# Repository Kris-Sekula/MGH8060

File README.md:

# MGH8060
SC/MP INS8060-based microcomputer running National Industrial Basic Language (NIBL)

Here is an overview of the device:

And here is my assembled unit - hardware v1.2

## Bill of Materials

| Component type     | Reference | Description                                   | Quantity |
| ------------------ | --------- | --------------------------------------------- | -------- |
| PCB                |           | [Order from PCBWay](https://www.pcbway.com/project/shareproject/MGH8060_SC_MP_Microcomputer_731c2144.html)| 1        |
| Integrated Circuit | U1        | MAX232(A) - RS232 Driver, 16 pin DIP          | 1        | 
| Integrated Circuit | U2        | INS8060 - SC/MP II Microcontroller, 40 pin DIP    | 1        |
| Integrated Circuit | U3        | HM62256B - 32kb SRAM, 28 pin DIP    | 1        |
| Integrated Circuit | U4        | 74LS573 - high-speed octal latch, 20 pin DIP    | 1        |
| Integrated Circuit | U5        | 8255A - Programmable Peripheral Interface, 40 pin DIP    | 1        |
| Integrated Circuit | U6        | 27C512 - 64kb EPROM, 28 pin DIP    | 1        |
| Integrated Circuit | U7        | 74LS138 - 3-to-8 line decoder, 16 pin DIP    | 1        |
| Integrated Circuit | U8        | 74LS21 - Dual 4 -Input AND Logic, 14 pin DIP   | 1        |
| Integrated Circuit | U8        | 74LS04 - HEX Inverter, 14 pin DIP   | 1        |
| LED                | D1        | LED indicator, 3 mm                           | 1        |
| LED                | D2        | LED indicator, 3 mm                           | 1        |
| Diode                | D3        | 1N4002,  general-purpose diode    | 1        |
| Pin Header         | J1        | 2x17 header female, 2.54 mm pitch        | 1        |
| Connector         | J2        | Screw terminal        | 1        |
| Connector         | J3        | DB9 male        | 1        |
| Pin Header         | J4        | 1x6 pin header, 2.54 mm pitch, angle | 1 |
| Pin Header         | J5        | 2x25 header female, 2.54 mm pitch        | 1        |
| Pin Header         | J6        | 1x6 pin header, 2.54 mm pitch | 1 |
| Pin Header         | JP1        | 1x2 pin header, 2.54 mm pitch | 1 |
| Pin Header         | JP2-JP4        | 1x3 pin header, 2.54 mm pitch | 3 |
| Capacitor          | C8-C15   | 1 uF, 16V, electrolytic, 2.54 mm pitch                  | 5       |
| Capacitor          | C6       | 27pF, ceramic, 2.54 mm pitch                | 1        |
| Capacitor          | C8-C15   | 0.1 uF, 50V, MLCC, 5 mm pitch                 | 8        |
| Capacitor          | C7,C20   | 22uF, 6.8V, electrolytic, 2.54 mm pitch                | 2        |
| Resistor           | R1   | 160 kohm, 0.125 W, axial                       | 1        |
| Resistor           | R2-R4,R8   | 1 kohm, 0.125 W, axial                       | 4        |
| Resistor           | R5   | 10k kohm, 0.125 W, axial                       | 1        |
| Resistor           | R9   | 4.7k kohm, 0.125 W, axial                       | 1        |
| Crystal           | X1   | 4MHz, short 3.5mm heigh max                       | 1        |
| IC Socket          | U8,U9     | 14 pin DIP                                    | 2       |
| IC Socket          | U1,U7    | 16 pin DIP                                    | 2        |
| IC Socket          | U4     | 20 pin DIP                                    | 1        |
| IC Socket          | U3,U6     | 28 pin DIP                                    | 2        |
| IC Socket          | U2,U5     | 40 pin DIP                                    | 2        |

## Memory Map

| Start | End | RAM | ROM | I/O |
| :------: | :------: | :----: | :----: | :----: |
| 0x0000 | 0x1FFF |  | X |  |			
| 0x2000 | 0x3FFF | X |  |  |			
| 0x4000 | 0x5FFF | X |  |  |			
| 0x6000 | 0x7FFF | X |  |  |			
| 0x8000 | 0x9FFF |  | X |  |			
| 0xA000 | 0xBFFF |  |  | X |			
| 0xC000 | 0xDFFF |  | X |  |			
| 0xE000 | 0xFFFF |  | X |  |

| Address | 8255 Function |
| :---: | :---: |
| 0xA000 | Port A |
| 0xA001 | Port B |
| 0xA002 | Port C |
| 0xA003 | Ctrl Register |

### Schematic
[Schematic - Version 1.2](Hardware/mgh8060_v1.2.pdf)

### Credits
* The device is based on the work of [Ronald Dekker](https://www.dos4ever.com/SCMP/SCMP.html#circuit)

* Early versions of my design were reviewed by Phil(aka [Retro Phil](https://www.mccrash-racing.co.uk/philg/picl/picl.htm)) who offered a lot of helpful suggestions, he also contributed all the firmware for MGH8060

## Release Notes

I used HCT parts for most of the ICs. Power usage was about 60mA

I used Winbond W27C512 (EEPROM pin compatible with EPROMs)

Please consider getting the PCB from my sponsor PCBWay

If you found this helpful and you like the work I do, why not buy me a coffee, thanks! :)

### Changes
* Version 1.2:
  
  * Fixed missing connections. 

* Version 1.1:
  
  * Corrected CE signals (thanks Phil)

* Version 1.0
  
  * Initial version

## License

Copyright 2024 Kris Sekula

This work is licensed under a [Creative Commons Attribution-NonCommercial 4.0 International (CC BY-NC 4.0) ](https://creativecommons.org/licenses/by-nc/4.0/).

### Trademarks

* Other names and brands may be claimed as the property of others.

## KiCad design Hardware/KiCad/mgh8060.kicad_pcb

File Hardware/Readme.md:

In the KiCad folder, you can find the KiCad sources for the PCB v1.2. 

## __Before you download the files, please consider ordering the PCBs from *PCBWay* by following this [-> link <-](https://www.pcbway.com/project/shareproject/MGH8060_SC_MP_Microcomputer_731c2144.html).__

I get a small portion of your order that I can use towards my future open-source projects, and more importantly, PCBWay will be more likely to sponsor me again.

Thanks again to PCBWay for sponsoring the PCBs used in this project.

If you found this helpful and you like the work I do, why not buy me a coffee, thanks! :)

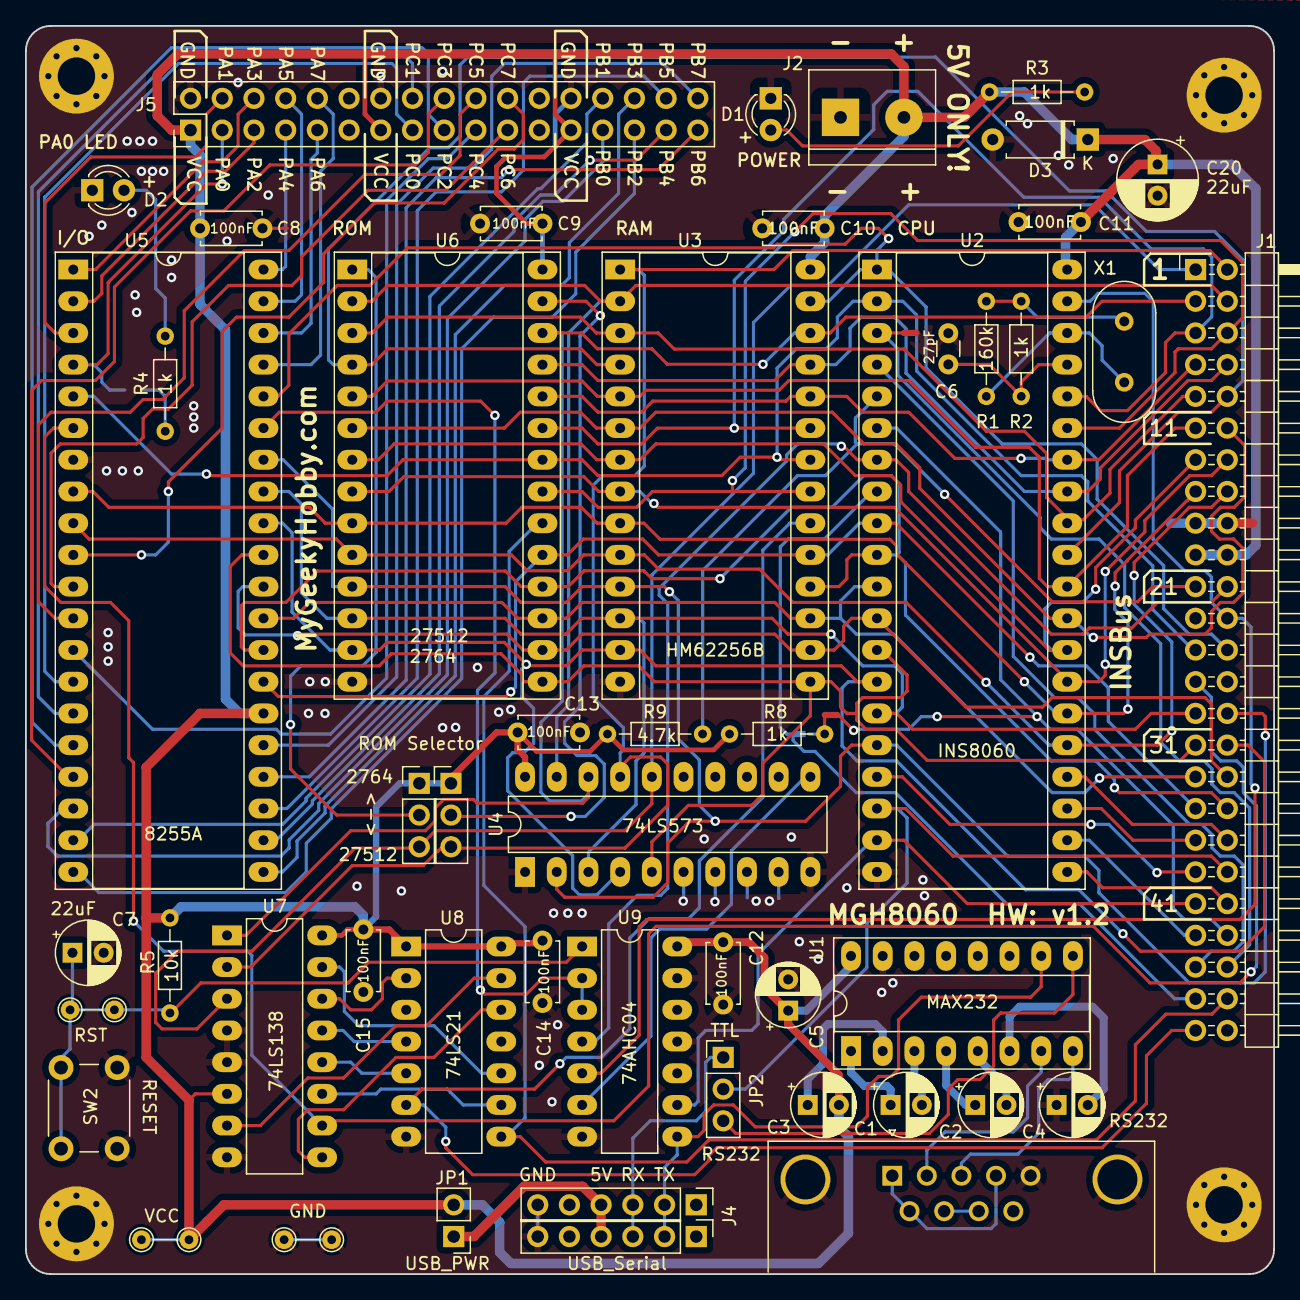
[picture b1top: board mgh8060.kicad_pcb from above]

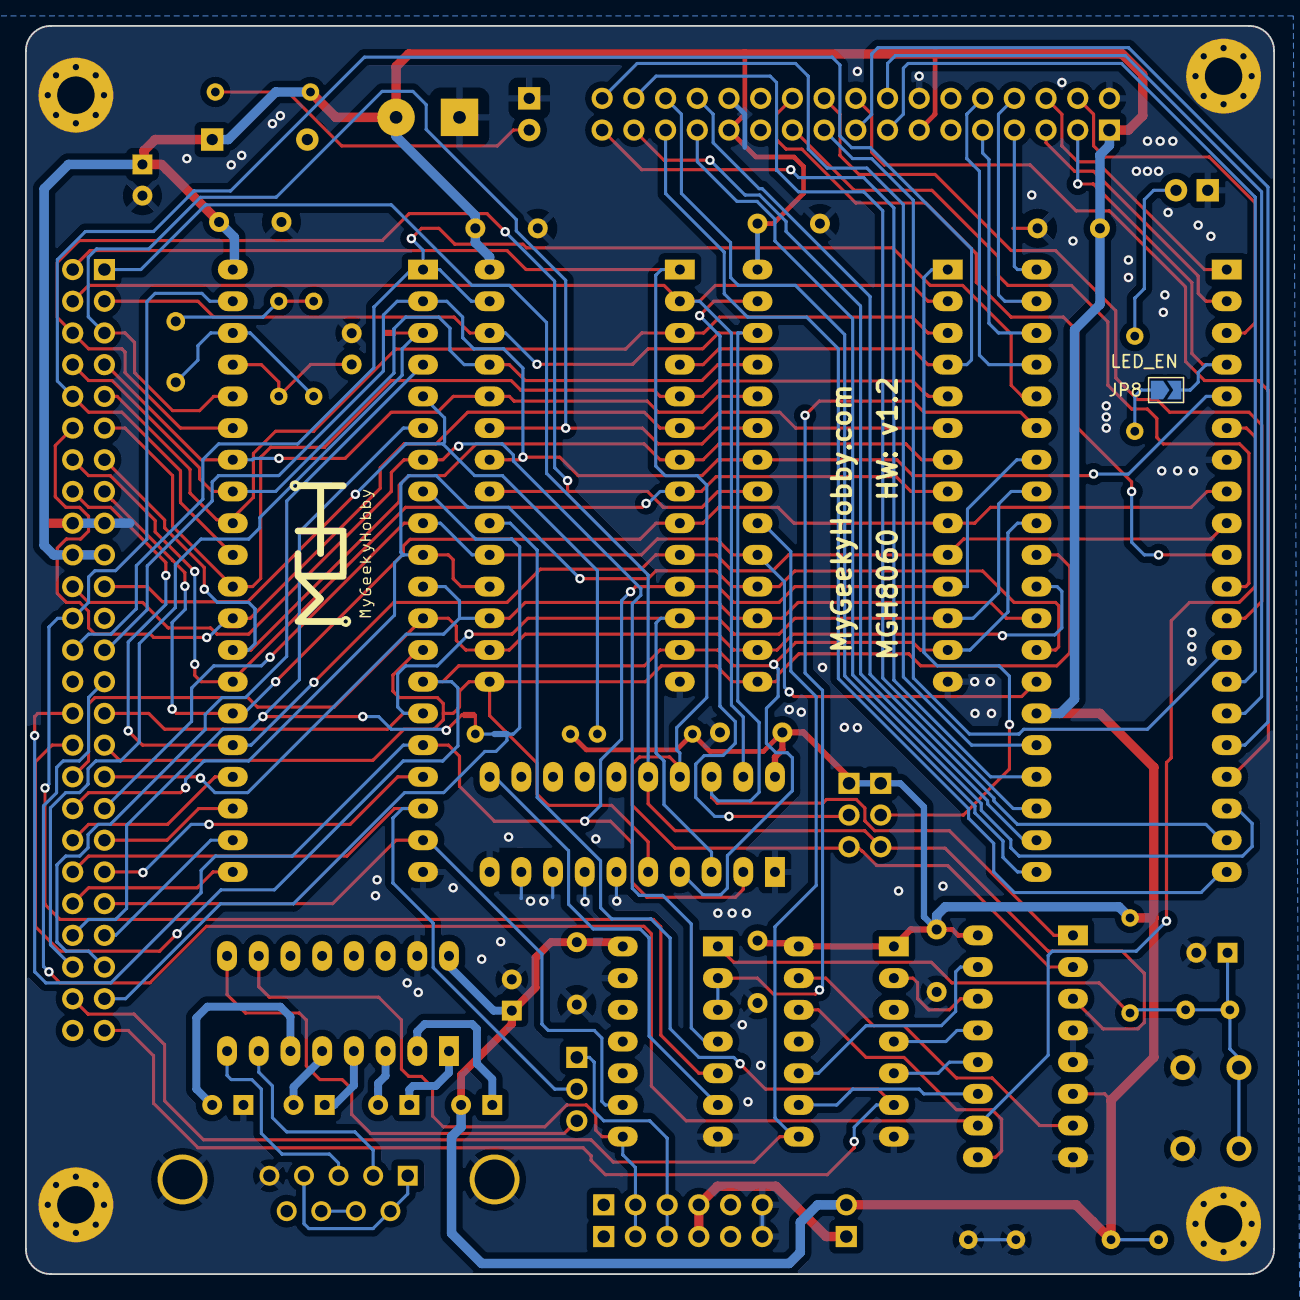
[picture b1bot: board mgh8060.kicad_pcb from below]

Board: 2 copper layers, 100.0 x 100.0 mm, 61 parts (2 on the bottom side), 102 nets.

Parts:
C1, C2, C3, C4, C5: 1uF; CP_Radial_D5.0mm_P2.50mm
C6: 27pF; C_Disc_D3.0mm_W1.6mm_P2.50mm
C7: 22uF; CP_Radial_D5.0mm_P2.50mm
C8, C9, C10, C11, C12, C13, C14, C15: 100nF; C_Disc_D4.7mm_W2.5mm_P5.00mm
C20: 22uF; CP_Radial_D6.3mm_P2.50mm
D1, D2: LED; LED_D3.0mm
D3: 1N4002; D_A-405_P7.62mm_Horizontal
H1, H2, H3, H4: MountingHole_Pad; MountingHole_3mm_Pad_Via
J1: Z80Bus; PinHeader_2x25_P2.54mm_Horizontal
J2: Screw_Terminal_01x02; TerminalBlock_bornier-2_P5.08mm
J3: DB9_Male; DSUB-9_Male_Horizontal_P2.77x2.84mm_EdgePinOffset4.94mm_Hou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
J4, J6: FTDI; PinHeader_1x06_P2.54mm_Vertical
J5: Conn_02x15_Odd_Even; PinHeader_2x17_P2.54mm_Vertical
JP1: VCC_EN; PinHeader_1x02_P2.54mm_Vertical
JP2: RX_Select; PinHeader_1x03_P2.54mm_Vertical
JP3: Pin27_Select; PinHeader_1x03_P2.54mm_Vertical
JP4: Pin1_Select; PinHeader_1x03_P2.54mm_Vertical
JP8: LED_EN; SolderJumper-2_P1.3mm_Open_TrianglePad1.0x1.5mm
NT1, NT2, NT3: NetTie_2; NetTie-2_SMD_Pad0.5mm
R1: 160k; R_Axial_DIN0204_L3.6mm_D1.6mm_P7.62mm_Horizontal
R2, R3, R4, R8: 1k; R_Axial_DIN0204_L3.6mm_D1.6mm_P7.62mm_Horizontal
R5: 10k; R_Axial_DIN0204_L3.6mm_D1.6mm_P7.62mm_Horizontal
R9: 4.7k; R_Axial_DIN0204_L3.6mm_D1.6mm_P7.62mm_Horizontal
SW2: SW_Push; SW_PUSH_6mm
TP1, TP3, TP7, TP8: 5V VCC; TestPoint_THTPad_D1.5mm_Drill0.7mm
TP2, TP4: GND; TestPoint_THTPad_D1.5mm_Drill0.7mm
U1: MAX232; DIP-16_W7.62mm_Socket_LongPads
U2: INS8060; DIP-40_W15.24mm_Socket_LongPads
U3: HM62256B; DIP-28_W15.24mm_Socket_LongPads
U4: 74LS573; DIP-20_W7.62mm_LongPads
U5: 8255A; DIP-40_W15.24mm_Socket_LongPads
U6: 27C512; DIP-28_W15.24mm_Socket_LongPads
U7: 74LS138; DIP-16_W7.62mm_LongPads
U8: 74LS21; DIP-14_W7.62mm_LongPads
U9: 74AHC04; DIP-14_W7.62mm_LongPads
X1: 4MHz; Crystal_HC49-U_Vertical

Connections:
/A0: J1.16 (A0), U2.25 (A0), U3.10 (A0), U5.9 (A0), U6.10 (A0)
/A1: J1.15 (A1), U2.26 (A1), U3.9 (A1), U5.8 (A1), U6.9 (A1)
/A2: J1.14 (A2), U2.27 (A2), U3.8 (A2), U6.8 (A2)
/A3: J1.13 (A3), U2.28 (A3), U3.7 (A3), U6.7 (A3)
/A4: J1.12 (A4), U2.29 (A4), U3.6 (A4), U6.6 (A4)
/A5: J1.11 (A5), U2.30 (A5), U3.5 (A5), U6.5 (A5)
/A6: J1.10 (A6), U2.31 (A6), U3.4 (A6), U6.4 (A6)
/A7: J1.9 (A7), U2.32 (A7), U3.3 (A7), U6.3 (A7)
/A8: J1.8 (A8), U2.33 (A8), U3.25 (A8), U6.25 (A8)
/A9: J1.7 (A9), U2.34 (A9), U3.24 (A9), U6.24 (A9)
/A10: J1.6 (A10), U2.35 (A10), U3.21 (A10), U6.21 (A10)
/A11: J1.5 (A11), U2.36 (A11), U3.23 (A11), U6.23 (A11)
/A12: J1.4 (A12), U3.2 (A12), U4.19 (Q0), U6.2 (A12)
/A13: J1.3 (A13), U3.26 (A13), U4.18 (Q1), U6.26 (A13), U7.1 (A0)
/A14: J1.2 (A14), JP3.3 (B), U3.1 (A14), U4.17 (Q2), U7.2 (A1)
/A15: J1.1 (A15), JP4.3 (B), U4.16 (Q3), U7.3 (A2)
/CONT: J1.47 (CONT), NT1.2, U2.8 (CONT)
/D0: J1.30 (D0), U2.16 (D0), U3.11 (D0), U4.2 (D0), U5.34 (D0), U6.11 (D0)
/D1: J1.29 (D1), U2.15 (D1), U3.12 (D1), U4.3 (D1), U5.33 (D1), U6.12 (D1)
/D2: J1.32 (D2), U2.14 (D2), U3.13 (D2), U4.4 (D2), U5.32 (D2), U6.13 (D2)
/D3: J1.31 (D3), U2.13 (D3), U3.15 (D3), U4.5 (D3), U5.31 (D3), U6.15 (D3)
/D4: J1.34 (D4), U2.12 (D4), U3.16 (D4), U5.30 (D4), U6.16 (D4)
/D5: J1.33 (D5), U2.11 (D5), U3.17 (D5), U5.29 (D5), U6.17 (D5)
/D6: J1.36 (D6), U2.10 (D6), U3.18 (D6), U5.28 (D6), U6.18 (D6)
/D7: J1.35 (D7), U2.9 (D7), U3.19 (D7), U5.27 (D7), U6.19 (D7)
/F0: J1.41 (F0), U2.19 (F0), U9.9
/F1: J1.42 (F1), U2.21 (F1)
/F2: J1.43 (F2), U2.22 (F2)
/PA0: J5.3, JP8.2 (B), U5.4 (PA0)
/PA1: J5.4, U5.3 (PA1)
/PA2: J5.5, U5.2 (PA2)
/PA3: J5.6, U5.1 (PA3)
/PA4: J5.7, U5.40 (PA4)
/PA5: J5.8, U5.39 (PA5)
/PA6: J5.9, U5.38 (PA6)
/PA7: J5.10, U5.37 (PA7)
/PB0: J5.27, U5.18 (PB0)
/PB1: J5.28, U5.19 (PB1)
/PB2: J5.29, U5.20 (PB2)
/PB3: J5.30, U5.21 (PB3)
/PB4: J5.31, U5.22 (PB4)
/PB5: J5.32, U5.23 (PB5)
/PB6: J5.33, U5.24 (PB6)
/PB7: J5.34, U5.25 (PB7)
/PC0: J5.15, U5.14 (PC0)
/PC1: J5.16, U5.15 (PC1)
/PC2: J5.17, U5.16 (PC2)
/PC3: J5.18, U5.17 (PC3)
/PC4: J5.19, U5.13 (PC4)
/PC5: J5.20, U5.12 (PC5)
/PC6: J5.21, U5.11 (PC6)
/PC7: J5.22, U5.10 (PC7)
/RESET: U5.35 (RESET), U9.2, U9.3
/ROM_1: JP4.2 (C), U6.1 (A15)
/ROM_27: JP3.2 (C), U6.27 (A14)
/RX_232: JP2.3 (B), U1.9 (R2OUT)
/RX_USB: J4.3, J6.3, JP2.1 (A)
/SA: J1.39 (SA), U2.17 (SA)
/SB: J1.40 (SB), JP2.2 (C), U2.18 (SB)
/SIN: J1.38 (SIN), U2.24 (SIN)
/SOUT: J1.37 (SOUT), U2.23 (SOUT)
/TX: J4.2, J6.2, U1.10 (T2IN), U9.8
/~ADS: J1.24 (~ADS), U2.39 (~ADS), U9.5
/~BREQ: J1.21 (~BREQ), R9.2, U2.5 (~BREQ)
/~ENIN: J1.46 (~ENIN), NT3.2, U2.3 (~ENIN)
/~ENOUT: J1.45 (~ENOUT), U2.4 (~ENOUT)
/~Ext_RESET: C7.1, R5.2, SW2.2, TP7.1, TP8.1, U9.1
/~HOLD: J1.44 (~HOLD), NT2.2, U2.6 (~HOLD)
/~IO_CS: J1.27 (~IO_CS), U5.6 (~CS), U7.10 (O5)
/~RAM_CS: J1.49 (USER2), U3.20 (~CS), U8.6
/~RDS: J1.25 (~MREQ), U2.2 (~RDS), U3.22 (~OE), U5.5 (~RD), U6.22 (~OE)
/~RESET: J1.22 (~Rst), U2.7 (~RST), U9.4
/~ROM_CS: J1.48 (USER1), U6.20 (~CE), U8.8
/~WDS: J1.26 (~WDS), U2.1 (~WDS), U3.27 (~WE), U5.36 (~WR)
GND: C4.1, C5.2, C6.2, C7.2, C8.2, C9.2, C10.2, C11.2, C12.2, C13.2, C14.2, C15.2, C20.2, D1.1 (K), D2.1 (K), D3.2 (A), H1.1, H2.1, H3.1, H4.1, J1.17 (GND), J1.18 (GND), J2.1, J3.0 (PAD), J3.5, J4.6, J5.2, J5.14, J5.26, J6.6, NT3.1, SW2.1, TP2.1, TP4.1, U1.15 (GND), U2.20 (GND), U3.14 (VSS), U4.1 (OE), U4.6 (D4), U4.7 (D5), U4.8 (D6), U4.9 (D7), U4.10 (GND), U5.7 (GND), U6.14 (GND), U7.4 (E1), U7.5 (E2), U7.8 (GND), U8.7 (GND), U9.7 (GND), U9.11, U9.13
unnamed: D1.2 (A), R3.2
unnamed: D2.2 (A), R4.2
unnamed: J3.1, J3.4, J3.6
unnamed: J3.7, J3.8
unnamed: J4.4, J6.4, JP1.1 (A)
unnamed: JP8.1 (A), R4.1
unnamed: NT1.1, NT2.1, R8.2
unnamed: R1.2, R2.1, X1.1
unnamed: C1.1, U1.1 (C1+)
unnamed: C1.2, U1.3 (C1-)
unnamed: C2.1, U1.4 (C2+)
unnamed: C2.2, U1.5 (C2-)
unnamed: J3.3, U1.8 (R2IN)
unnamed: J3.2, U1.7 (T2OUT)
unnamed: C3.1, U1.2 (VS+)
unnamed: C4.2, U1.6 (VS-)
unnamed: C6.1, R2.2, U2.37 (XIN)
unnamed: R1.1, U2.38 (XOUT), X1.2
unnamed: U4.11 (Load), U9.6
unnamed: U7.15 (O0), U8.10
unnamed: U7.14 (O1), U8.2
unnamed: U7.13 (O2), U8.4
unnamed: U7.12 (O3), U8.5
unnamed: U7.11 (O4), U8.9
unnamed: U7.9 (O6), U8.12
unnamed: U7.7 (O7), U8.13
VCC: C3.2, C5.1, C8.1, C9.1, C10.1, C11.1, C12.1, C13.1, C14.1, C15.1, C20.1, D3.1 (K), J1.19 (5V), J1.20 (5V), J2.2, J5.1, J5.13, J5.25, JP1.2 (B), JP3.1 (A), JP4.1 (A), R3.1, R5.1, R8.1, R9.1, TP1.1, TP3.1, U1.16 (VCC), U2.40 (VCC), U3.28 (VCC), U4.20 (VCC), U5.26 (VCC), U6.28 (VCC), U7.6 (E3), U7.16 (VCC), U8.1, U8.14 (VCC), U9.14 (VCC)

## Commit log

2024-01-28 Update README.md
    Added BOM
2024-01-28 Update README.md
    Added KoFi links
2024-01-28 Update README.md
    Added Address Map
2024-01-28 Added PCB files
2024-02-01 More Pictures
2024-02-01 Update README.md
    Added credits
